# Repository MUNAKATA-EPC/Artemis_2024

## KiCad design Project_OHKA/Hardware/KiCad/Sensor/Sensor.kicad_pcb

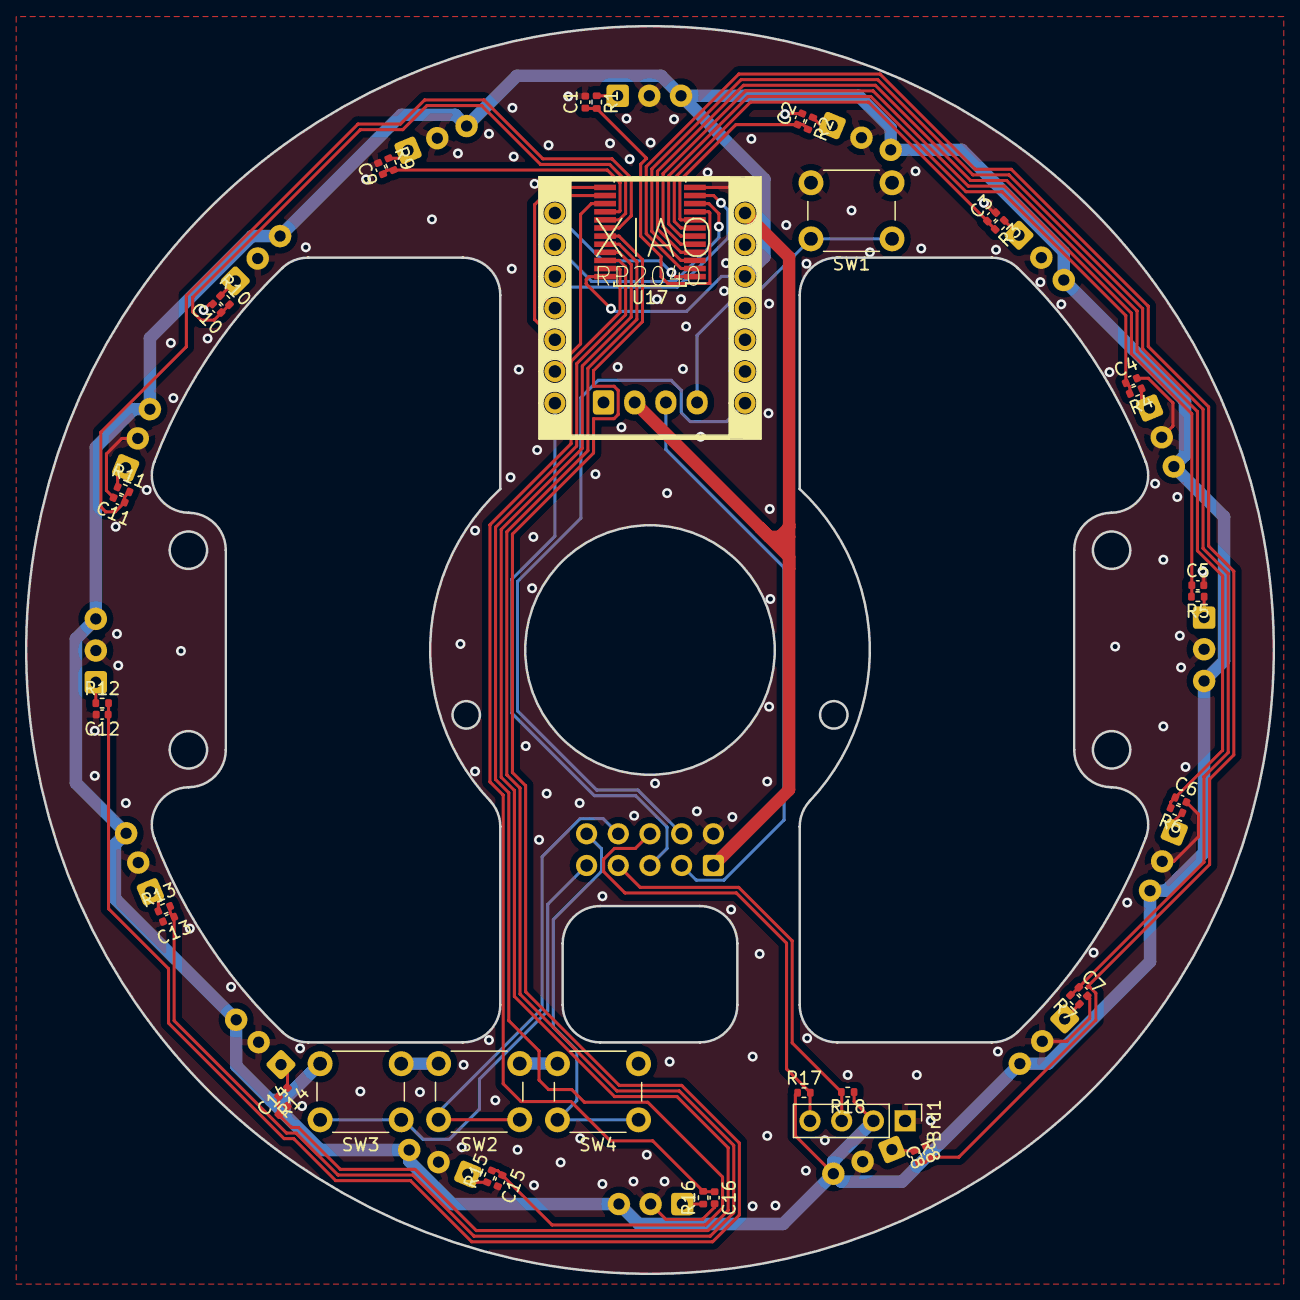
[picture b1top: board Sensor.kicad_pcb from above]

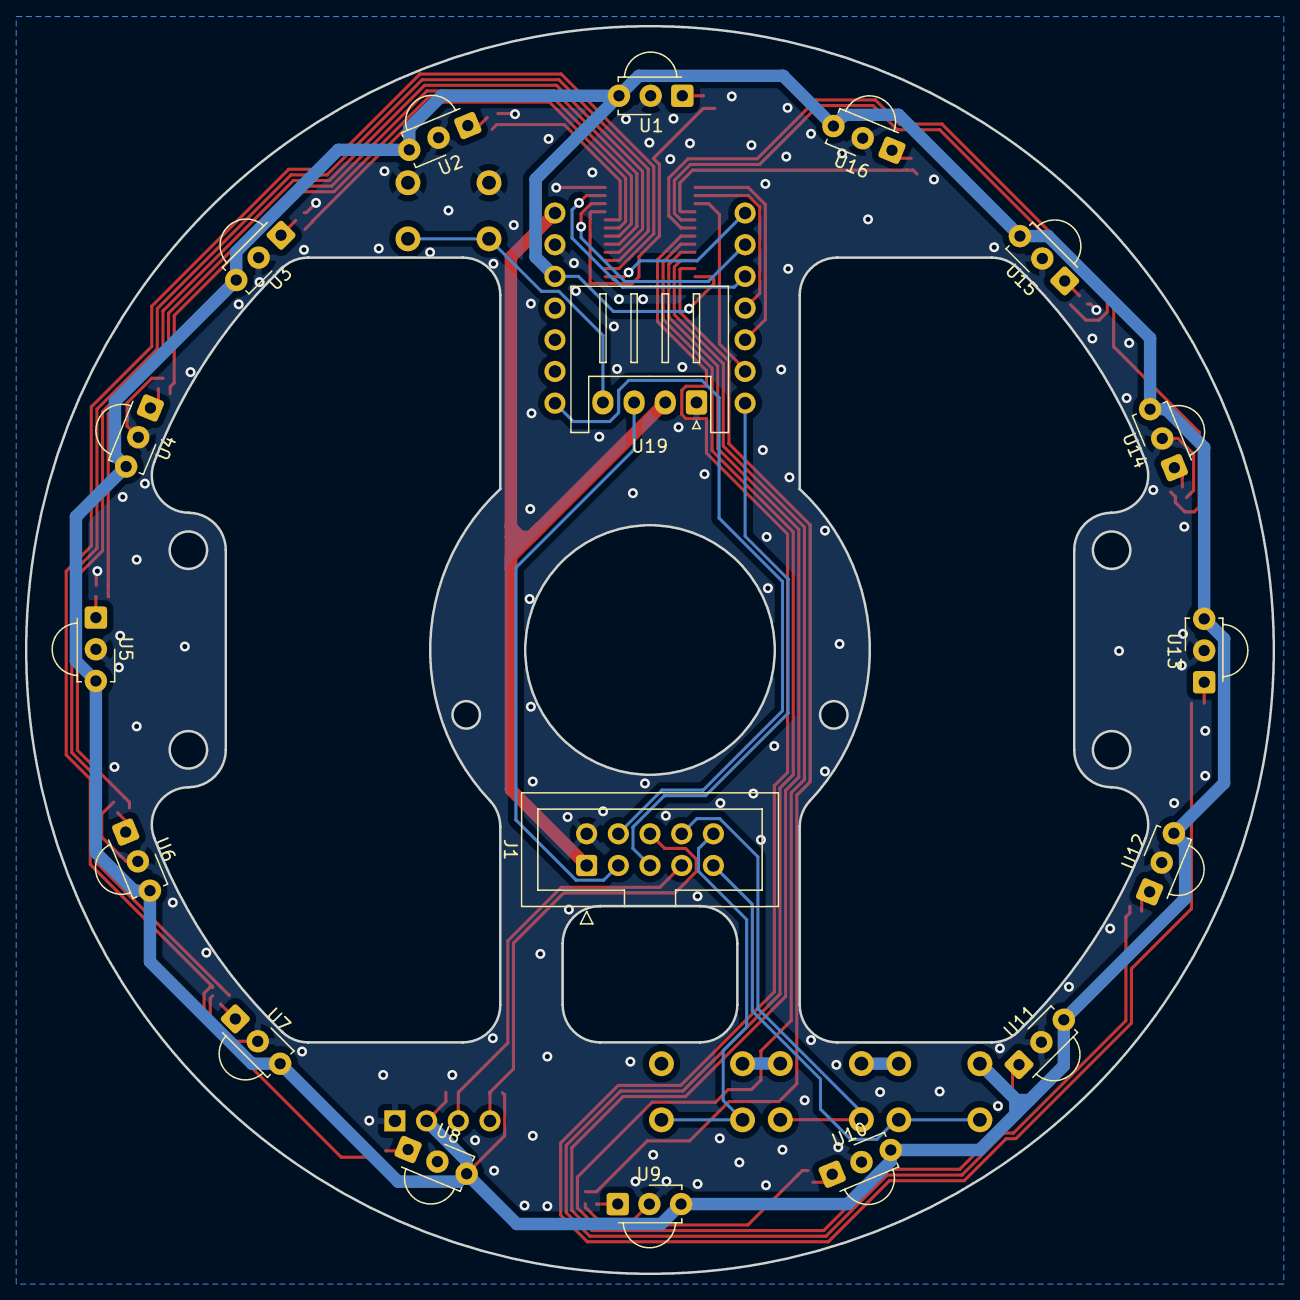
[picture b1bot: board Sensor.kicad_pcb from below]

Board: 2 copper layers, 100.0 x 100.0 mm, 59 parts (18 on the bottom side), 50 nets.

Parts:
Brd1: SSD1306; PinHeader_1x04_P2.54mm_Vertical
C1, C2, C3, C4, C5, C6, C7, C8, C9, C10, C11, C12, C13, C14, C15, C16: C_Small; C_0402_1005Metric
J1: Conn_01x10_Socket; IDC-Header_2x05_P2.54mm_Vertical
R1, R2, R3, R4, R5, R6, R7, R8, R9, R10, R11, R12, R13, R14, R15, R16, R17, R18: R; R_0402_1005Metric
SW1, SW2, SW3, SW4: SW_Push; SW_PUSH_6mm_H4.3mm
U1, U2, U3, U4, U5, U6, U7, U8, U9, U10, U11, U12, U13, U14, U15, U16: TSSP58038; Vishay_MINICAST-3Pin
U17: CD74HC4067SM; SSOP-24_5.3x8.2mm_P0.65mm
U18: Seeeduino_Xiao; seeeduinoXIAO
U19: open_mv; JST_XH_S4B-XH-A_1x04_P2.50mm_Horizontal

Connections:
+3.3V: Brd1.2 (VCC), R17.1, R18.1, SW2.2, SW3.2, SW4.2, U1.3 (Vs), U2.3 (Vs), U3.3 (Vs), U4.3 (Vs), U5.3 (Vs), U6.3 (Vs), U7.3 (Vs), U8.3 (Vs), U9.3 (Vs), U10.3 (Vs), U11.3 (Vs), U12.3 (Vs), U13.3 (Vs), U14.3 (Vs), U15.3 (Vs), U16.3 (Vs), U17.24 (VCC), U18.12 (3V3)
+5V: J1.1, U18.14 (5V), U19.2 (vin)
/1: C1.1, R1.2, U17.9 (I0)
/2: C2.1, R2.2, U17.8 (I1)
/3: C3.1, R3.2, U17.7 (I2)
/4: C4.1, R4.2, U17.6 (I3)
/5: C5.1, R5.2, U17.5 (I4)
/6: C6.1, R6.2, U17.4 (I5)
/7: C7.1, R7.2, U17.3 (I6)
/8: C8.1, R8.2, U17.2 (I7)
/9: C16.1, R16.2, U17.23 (I8)
/10: C15.1, R15.2, U17.22 (I9)
/11: C14.1, R14.2, U17.21 (I10)
/12: C13.1, R13.2, U17.20 (I11)
/13: C12.1, R12.2, U17.19 (I12)
/14: C11.1, R11.2, U17.18 (I13)
/15: C10.1, R10.2, U17.17 (I14)
/16: C9.1, R9.2, U17.16 (I15)
/CAM_RX: J1.3, U19.3 (seru01)
/DATA: U17.1 (COM), U18.1 (DAC)
/E: U17.15 (~E), U18.6 (SCL)
/IR_RX: J1.5, U18.7 (TX)
/IR_TX: J1.4, U18.8 (RX)
/LEFT: J1.9, SW3.1
/RIGHT: J1.10, SW4.1
/RUN: J1.8, SW2.1
/S0: U17.10 (S0), U18.2
/S1: U17.11 (S1), U18.3
/S2: U17.14 (S2), U18.4
/S3: U17.13 (S3), U18.5 (SDA)
/SCL: Brd1.3 (SCL), J1.7, R18.2
/SDA: Brd1.4 (SDA), J1.6, R17.2
GND: Brd1.1 (GND), C1.2, C2.2, C3.2, C4.2, C5.2, C6.2, C7.2, C8.2, C9.2, C10.2, C11.2, C12.2, C13.2, C14.2, C15.2, C16.2, J1.2, SW1.2, U1.2 (GND), U2.2 (GND), U3.2 (GND), U4.2 (GND), U5.2 (GND), U6.2 (GND), U7.2 (GND), U8.2 (GND), U9.2 (GND), U10.2 (GND), U11.2 (GND), U12.2 (GND), U13.2 (GND), U14.2 (GND), U15.2 (GND), U16.2 (GND), U17.12 (GND), U18.13 (GND), U19.1 (gnd)
unnamed: R1.1, U1.1 (OUT)
unnamed: R2.1, U2.1 (OUT)
unnamed: R3.1, U3.1 (OUT)
unnamed: R4.1, U4.1 (OUT)
unnamed: R5.1, U5.1 (OUT)
unnamed: R6.1, U6.1 (OUT)
unnamed: R7.1, U7.1 (OUT)
unnamed: R8.1, U8.1 (OUT)
unnamed: R16.1, U9.1 (OUT)
unnamed: R15.1, U10.1 (OUT)
unnamed: R14.1, U11.1 (OUT)
unnamed: R13.1, U12.1 (OUT)
unnamed: R12.1, U13.1 (OUT)
unnamed: R11.1, U14.1 (OUT)
unnamed: R10.1, U15.1 (OUT)
unnamed: R9.1, U16.1 (OUT)
unnamed: SW1.1, U19.4

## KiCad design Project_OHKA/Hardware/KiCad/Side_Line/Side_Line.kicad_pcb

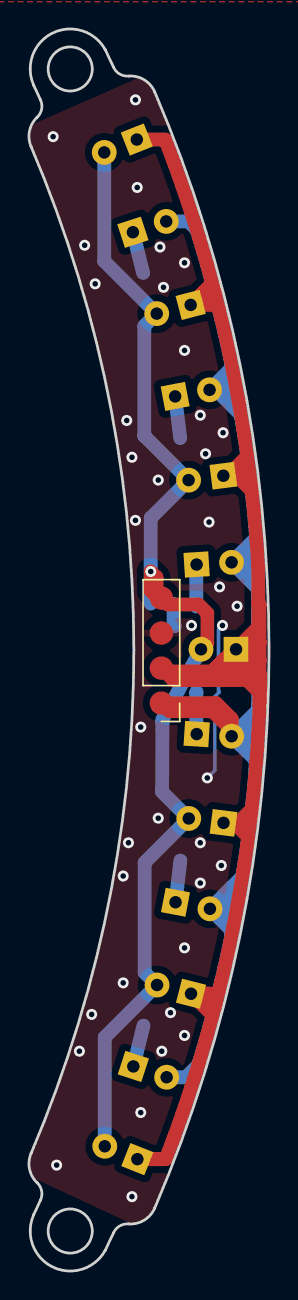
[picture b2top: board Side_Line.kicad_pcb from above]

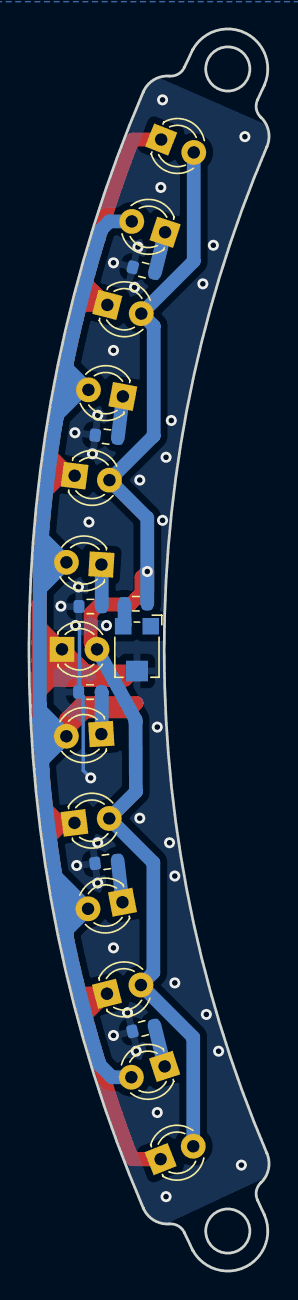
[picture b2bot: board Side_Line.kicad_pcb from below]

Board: 2 copper layers, 17.4 x 90.0 mm, 22 parts (21 on the bottom side), 11 nets.

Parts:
D1, D2, D3, D4, D5, D6: LED; LED_D3.0mm_Clear
J1: Conn_01x04_Socket; PinHeader_1x04_P2.54mm_Vertical
Q1, Q2, Q3, Q4, Q5, Q6, Q7: Q_Photo_NPN; LED_D3.0mm_Clear
R1, R2, R3, R4, R5, R6, R7: R; R_0603_1608Metric
RV1: R_Potentiometer_Trim_US; Potentiometer_Bourns_TC33X_Vertical

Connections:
+3.3V: J1.2, Q1.1 (C), Q2.1 (C), Q3.1 (C), Q4.1 (C), Q5.1 (C), Q6.1 (C), Q7.1 (C)
+5V: D1.2 (A), D2.2 (A), D3.2 (A), D4.2 (A), D5.2 (A), D6.2 (A), J1.1
/signal: J1.4, Q1.2 (E), Q2.2 (E), Q3.2 (E), Q4.2 (E), Q5.2 (E), Q6.2 (E), Q7.2 (E), R7.2
GND: J1.3, R1.2, R2.2, R3.2, R4.2, R5.2, R6.2, RV1.2
unnamed: D1.1 (K), R1.1
unnamed: D2.1 (K), R2.1
unnamed: D3.1 (K), R3.1
unnamed: D4.1 (K), R4.1
unnamed: D5.1 (K), R5.1
unnamed: D6.1 (K), R6.1
unnamed: R7.1, RV1.3

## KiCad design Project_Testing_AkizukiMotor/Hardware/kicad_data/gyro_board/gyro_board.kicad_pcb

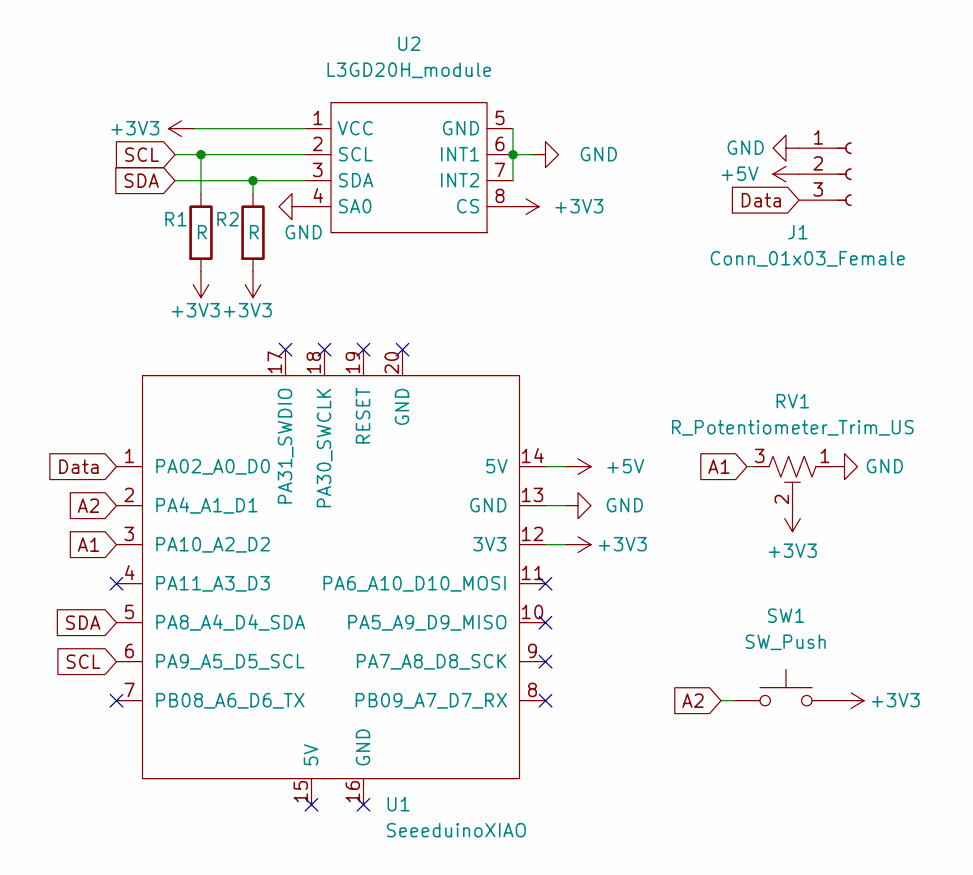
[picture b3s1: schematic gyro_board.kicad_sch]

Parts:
J1: Conn_01x03_Female; PinSocket_1x03_P2.54mm_Vertical
R1, R2: R; R_Axial_DIN0204_L3.6mm_D1.6mm_P5.08mm_Horizontal
RV1: R_Potentiometer_Trim_US; TA48033S
SW1: SW_Push; SW_PUSH_6mm_H7.3mm
U1: SeeeduinoXIAO; seeeduinoXIAO
U2: L3GD20H_module; L3GD20H

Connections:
+3V3: R1.2, R2.2, RV1.2, SW1.2, U1.12 (3V3), U2.1 (VCC), U2.8 (CS)
+5V: J1.2, U1.14 (5V)
A1: RV1.3, U1.3 (PA10_A2_D2)
A2: SW1.1, U1.2 (PA4_A1_D1)
Data: J1.3, U1.1 (PA02_A0_D0)
GND: J1.1, RV1.1, U1.13 (GND), U2.4 (SA0), U2.5 (GND), U2.6 (INT1), U2.7 (INT2)
SCL: R1.1, U1.6 (PA9_A5_D5_SCL), U2.2 (SCL)
SDA: R2.1, U1.5 (PA8_A4_D4_SDA), U2.3 (SDA)

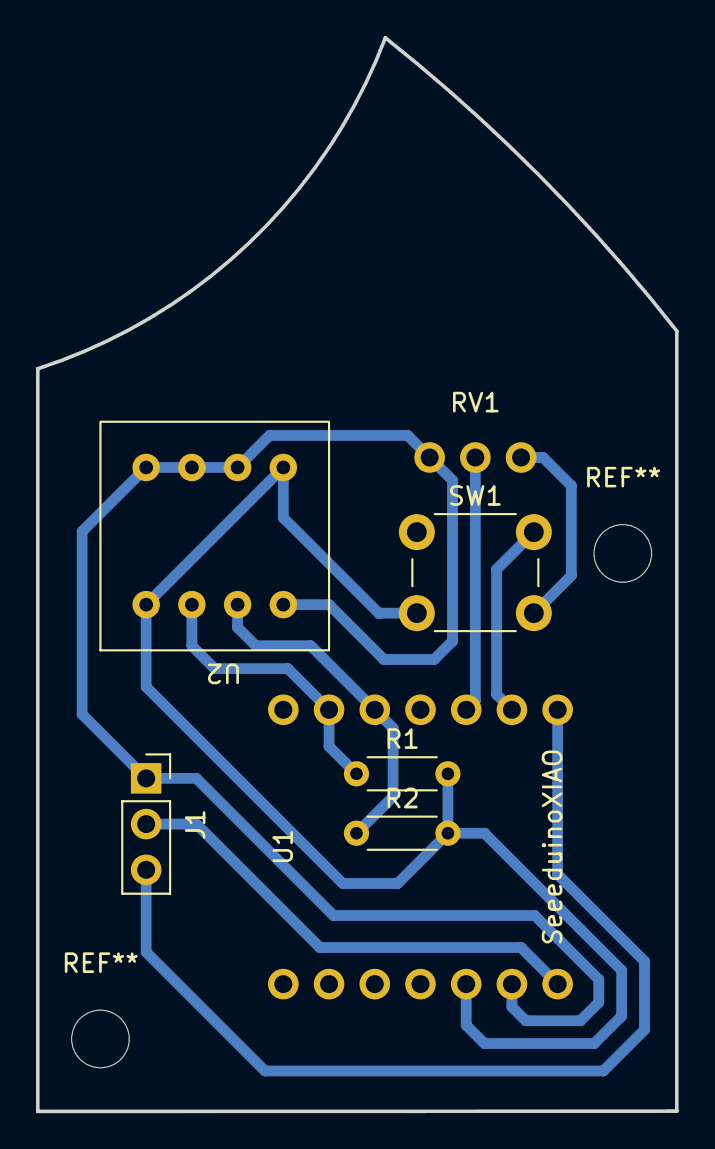
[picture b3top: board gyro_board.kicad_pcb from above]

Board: 2 copper layers, 35.5 x 59.6 mm, 7 parts (0 on the bottom side), 8 nets.

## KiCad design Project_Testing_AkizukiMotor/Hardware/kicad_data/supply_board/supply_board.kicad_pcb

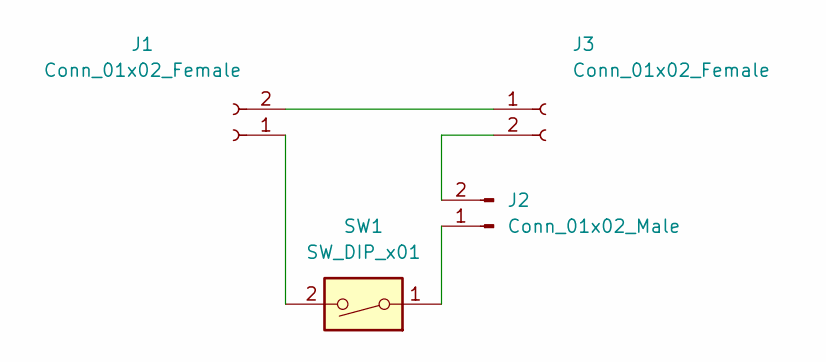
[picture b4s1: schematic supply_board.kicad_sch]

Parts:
J1, J3: Conn_01x02_Female; PinSocket_1x02_P2.54mm_Vertical
J2: Conn_01x02_Male; PinSocket_1x02_P2.54mm_Vertical
SW1: SW_DIP_x01; DS-850k

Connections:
unnamed: J1.1, SW1.2
unnamed: J1.2, J3.1
unnamed: J2.1, SW1.1
unnamed: J2.2, J3.2

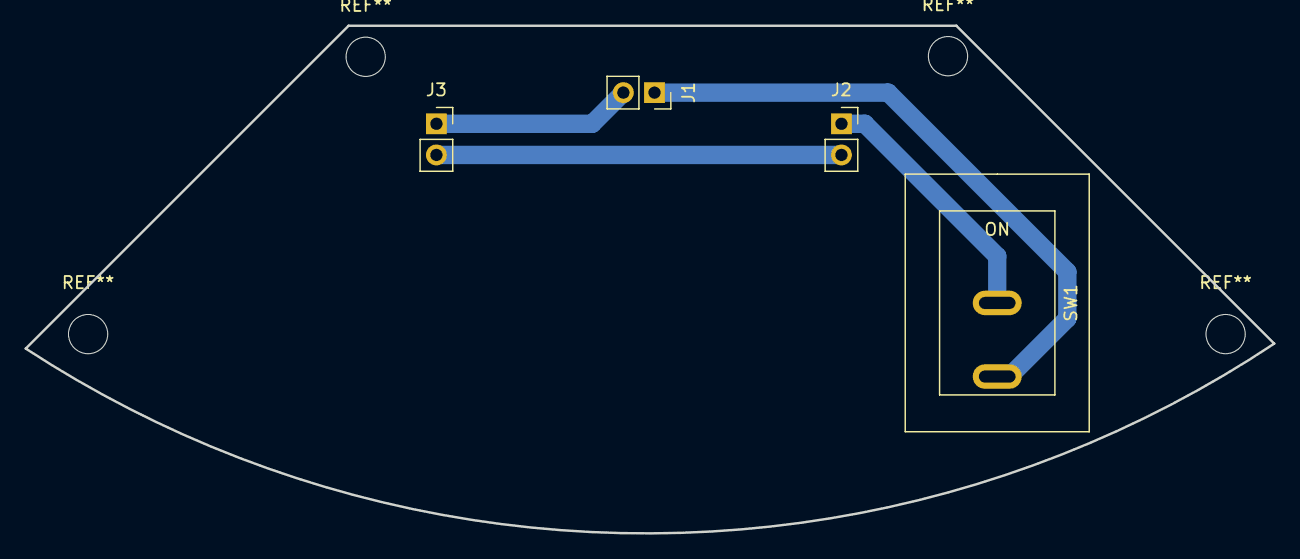
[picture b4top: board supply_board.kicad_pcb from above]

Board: 2 copper layers, 101.8 x 41.4 mm, 4 parts (0 on the bottom side), 4 nets.
